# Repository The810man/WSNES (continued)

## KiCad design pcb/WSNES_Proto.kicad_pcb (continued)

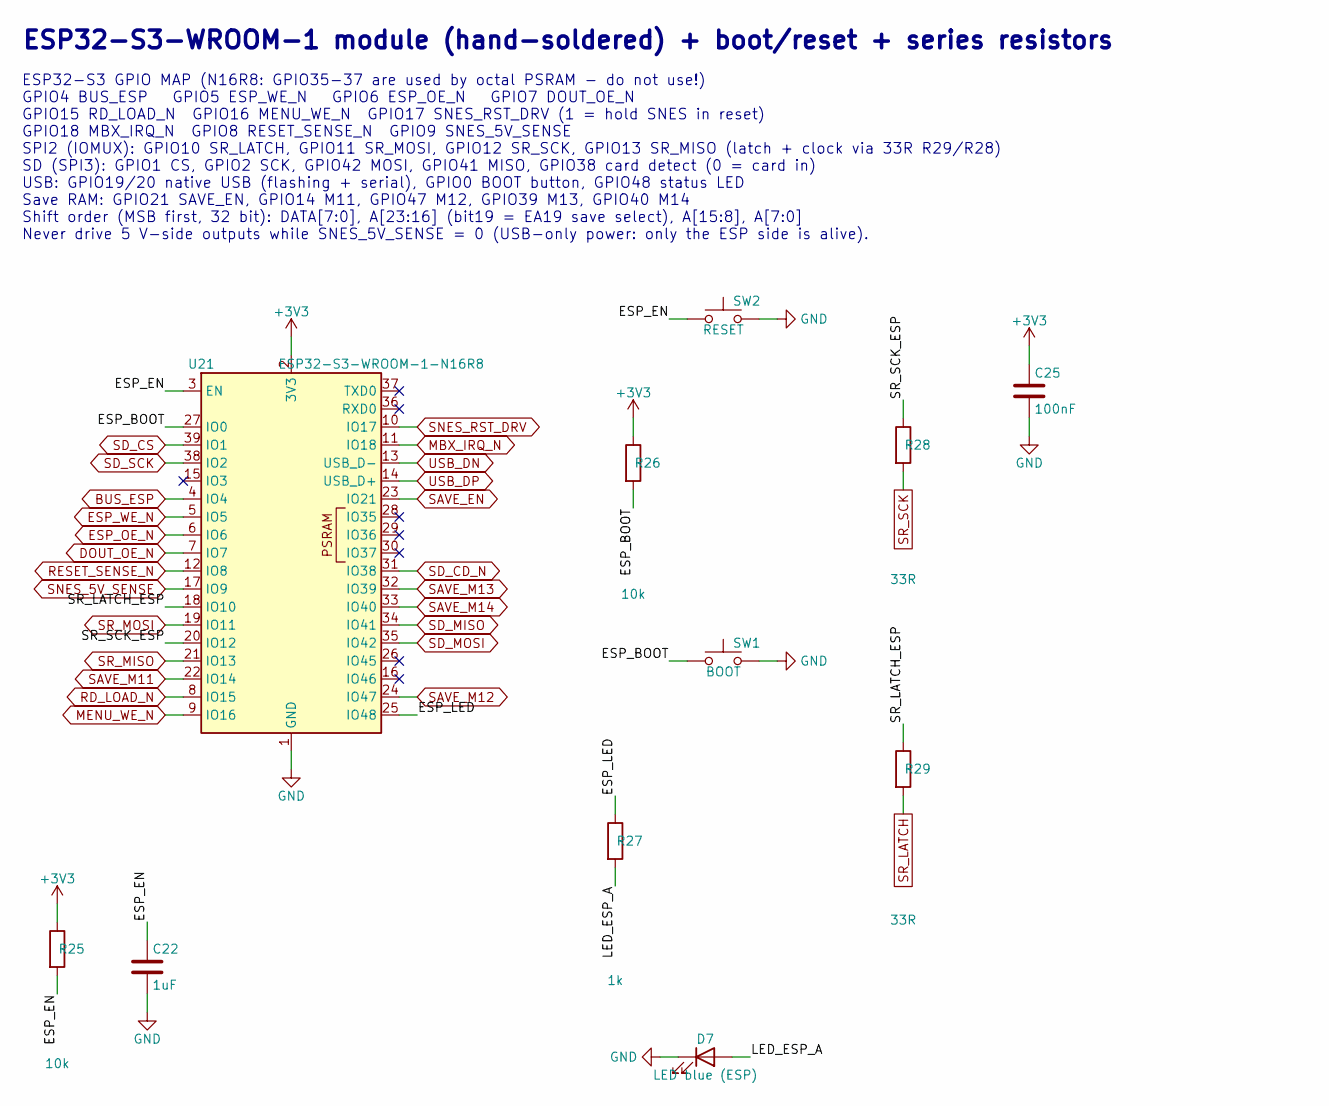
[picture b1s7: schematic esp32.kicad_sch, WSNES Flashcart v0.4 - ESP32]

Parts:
C22: 1uF; C_0603_1608Metric; MPN CL10A105KB8NNNC; LCSC C15849
C25: 100nF; C_0603_1608Metric; MPN CC0603KRX7R9BB104; LCSC C14663
D7: LED blue (ESP); LED_0603_1608Metric; MPN KT-0603B; LCSC C2288
R25, R26: 10k; R_0603_1608Metric; MPN 0603WAF1002T5E; LCSC C25804
R27: 1k; R_0603_1608Metric; MPN 0603WAF1001T5E; LCSC C21190
R28, R29: 33R; R_0603_1608Metric; MPN 0603WAF330JT5E; LCSC C23140
SW1: BOOT; SW_SPST_PTS810; MPN PTS810SJK250SMTRLFS; LCSC C221896
SW2: RESET; SW_SPST_PTS810; MPN PTS810SJK250SMTRLFS; LCSC C221896
U21: ESP32-S3-WROOM-1-N16R8; ESP32-S3-WROOM-1; MPN ESP32-S3-WROOM-1-N16R8; LCSC C2913202

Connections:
+3V3: C25.1, R25.1, R26.1, U21.2 (3V3); also elsewhere on the board
/ESP32/ESP_BOOT: R26.2, SW1.1, U21.27 (IO0)
/ESP32/ESP_EN: C22.1, R25.2, SW2.1, U21.3 (EN)
/ESP32/ESP_LED: R27.1, U21.25 (IO48)
/ESP32/LED_ESP_A: D7.2 (A), R27.2
/ESP32/SR_LATCH_ESP: R29.1, U21.18 (IO10)
/ESP32/SR_SCK_ESP: R28.1, U21.20 (IO12)
BUS_ESP: U21.4 (IO4); also elsewhere on the board
DOUT_OE_N: U21.7 (IO7); also elsewhere on the board
ESP_OE_N: U21.6 (IO6); also elsewhere on the board
ESP_WE_N: U21.5 (IO5); also elsewhere on the board
GND: C22.2, C25.2, D7.1 (K), SW1.2, SW2.2, U21.1 (GND), U21.40 (GND), U21.41 (GND); also elsewhere on the board
MBX_IRQ_N: U21.11 (IO18); also elsewhere on the board
MENU_WE_N: U21.9 (IO16); also elsewhere on the board
RD_LOAD_N: U21.8 (IO15); also elsewhere on the board
RESET_SENSE_N: U21.12 (IO8); also elsewhere on the board
SAVE_EN: U21.23 (IO21); also elsewhere on the board
SAVE_M11: U21.22 (IO14); also elsewhere on the board
SAVE_M12: U21.24 (IO47); also elsewhere on the board
SAVE_M13: U21.32 (IO39); also elsewhere on the board
SAVE_M14: U21.33 (IO40); also elsewhere on the board
SD_CD_N: U21.31 (IO38); also elsewhere on the board
SD_CS: U21.39 (IO1); also elsewhere on the board
SD_MISO: U21.34 (IO41); also elsewhere on the board
SD_MOSI: U21.35 (IO42); also elsewhere on the board
SD_SCK: U21.38 (IO2); also elsewhere on the board
SNES_5V_SENSE: U21.17 (IO9); also elsewhere on the board
SNES_RST_DRV: U21.10 (IO17); also elsewhere on the board
SR_LATCH: R29.2; also elsewhere on the board
SR_MISO: U21.21 (IO13); also elsewhere on the board
SR_MOSI: U21.19 (IO11); also elsewhere on the board
SR_SCK: R28.2; also elsewhere on the board
USB_DN: U21.13 (USB_D-); also elsewhere on the board
USB_DP: U21.14 (USB_D+); also elsewhere on the board

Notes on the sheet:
ESP32-S3-WROOM-1 module (hand-soldered) + boot/reset + series resistors
ESP32-S3 GPIO MAP (N16R8: GPIO35-37 are used by octal PSRAM - do not use!) GPIO4 BUS_ESP GPIO5 ESP_WE_N GPIO6 ESP_OE_N GPIO7 DOUT_OE_N GPIO15 RD_LOAD_N GPIO16 MENU_WE_N GPIO17 SNES_RST_DRV (1 = hold SNES in reset) GPIO18 MBX_IRQ_N GPIO8 RESET_SENSE_N GPIO9 SNES_5V_SENSE SPI2 (IOMUX): GPIO10 SR_LATC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

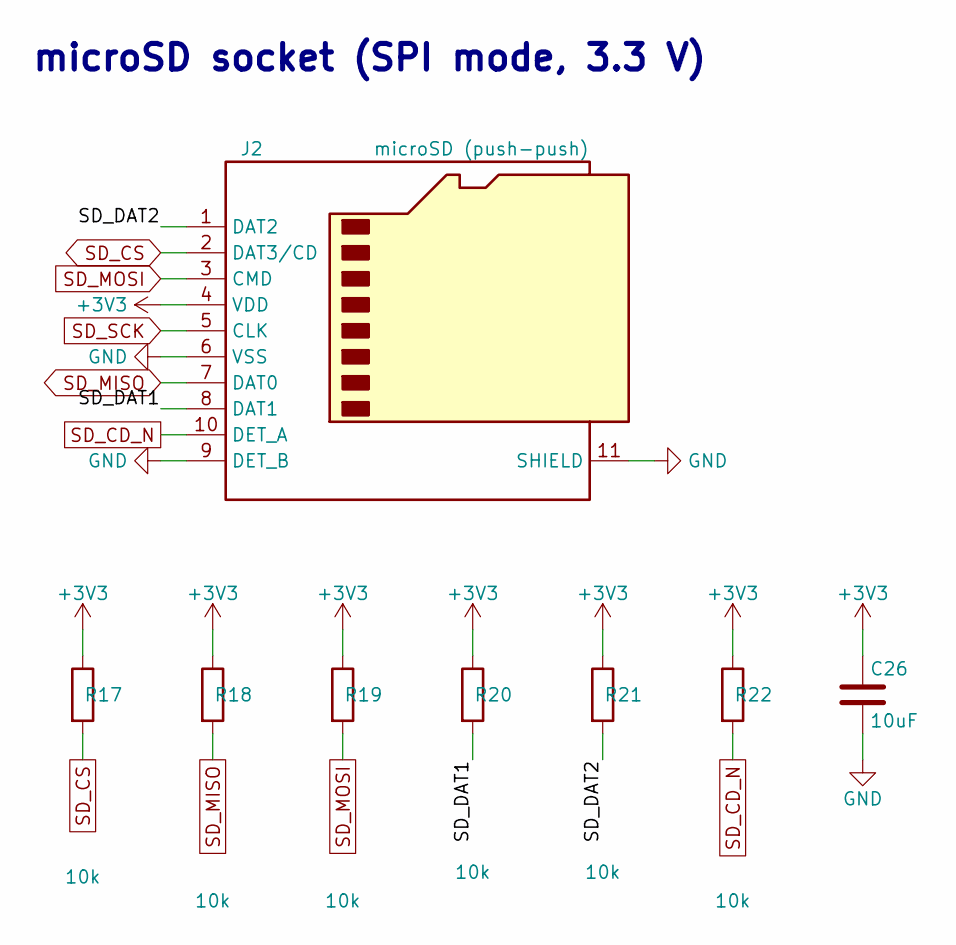
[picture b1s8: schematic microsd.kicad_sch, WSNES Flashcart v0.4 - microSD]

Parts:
C26: 10uF; C_0805_2012Metric; MPN CL21A106KAYNNNE; LCSC C15850
J2: microSD (push-push); microSD_HC_Hirose_DM3AT-SF-PEJM5; MPN DM3AT-SF-PEJM5; LCSC C114218
R17, R18, R19, R20, R21, R22: 10k; R_0603_1608Metric; MPN 0603WAF1002T5E; LCSC C25804

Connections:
+3V3: C26.1, J2.4 (VDD), R17.1, R18.1, R19.1, R20.1, R21.1, R22.1; also elsewhere on the board
/microSD/SD_DAT1: J2.8 (DAT1), R20.2
/microSD/SD_DAT2: J2.1 (DAT2), R21.2
GND: C26.2, J2.6 (VSS), J2.9 (DET_B), J2.11 (SHIELD); also elsewhere on the board
SD_CD_N: J2.10 (DET_A), R22.2; also elsewhere on the board
SD_CS: J2.2 (DAT3/CD), R17.2; also elsewhere on the board
SD_MISO: J2.7 (DAT0), R18.2; also elsewhere on the board
SD_MOSI: J2.3 (CMD), R19.2; also elsewhere on the board
SD_SCK: J2.5 (CLK); also elsewhere on the board

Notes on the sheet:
microSD socket (SPI mode, 3.3 V)

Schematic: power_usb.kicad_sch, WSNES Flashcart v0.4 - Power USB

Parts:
C1, C2: 22uF; C_1206_3216Metric; MPN CL31A226KAHNNNE; LCSC C12891
C23: 10uF; C_0805_2012Metric; MPN CL21A106KAYNNNE; LCSC C15850
C24: 22uF; C_0805_2012Metric; MPN CL21A226MAQNNNE; LCSC C45783
D1, D6: 1N5819WS; D_SOD-323; MPN 1N5819WS; LCSC C191023
D2: LED red (5V); LED_0603_1608Metric; MPN KT-0603R; LCSC C2286
J5: USB-C; USB_C_Receptacle_HRO_TYPE-C-31-M-12; MPN TYPE-C-31-M-12; LCSC C165948
R5: 1k; R_0603_1608Metric; MPN 0603WAF1001T5E; LCSC C21190
R23, R24: 5.1k; R_0603_1608Metric; MPN 0603WAF5101T5E; LCSC C23186
U22: AP2112K-3.3; SOT-23-5; MPN AP2112K-3.3TRG1; LCSC C51118
U23: USBLC6-2SC6; SOT-23-6; MPN USBLC6-2SC6; LCSC C7519

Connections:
+3V3: C24.1, U22.5 (VOUT); also elsewhere on the board
+5V: C2.1, D1.2 (A), R5.1; also elsewhere on the board
/Power_USB/ESP_5V: C1.1, C23.1, D1.1 (K), D6.1 (K), U22.1 (VIN), U22.3 (EN)
/Power_USB/LED_PWR_A: D2.2 (A), R5.2
/Power_USB/USB_CC1: J5.A5 (CC1), R23.1
/Power_USB/USB_CC2: J5.B5 (CC2), R24.1
/Power_USB/VBUS: D6.2 (A), J5.A4 (VBUS), J5.A9 (VBUS), J5.B4 (VBUS), J5.B9 (VBUS), U23.5 (VBUS)
GND: C1.2, C2.2, C23.2, C24.2, D2.1 (K), J5.A1 (GND), J5.A12 (GND), J5.B1 (GND), J5.B12 (GND), J5.S1 (SHIELD), R23.2, R24.2, U22.2 (GND), U23.2 (GND); also elsewhere on the board
USB_DN: J5.A7 (D-), J5.B7 (D-), U23.3 (I/O2), U23.4 (I/O2); also elsewhere on the board
USB_DP: J5.A6 (D+), J5.B6 (D+), U23.1 (I/O1), U23.6 (I/O1); also elsewhere on the board

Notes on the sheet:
Power: SNES 5 V, USB-C (ESD, CC), 3.3 V LDO
SNES +5V and USB VBUS meet at ESP_5V through D1 / D6 (Schottky OR). U22 makes +3V3 for the ESP, the SD card and U14. U23 USBLC6 protects D+, D- and VBUS at the connector.

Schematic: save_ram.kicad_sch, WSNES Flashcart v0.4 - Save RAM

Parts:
BT1: CR2032; BatteryHolder_MYOUNG_BS-07-A1BJ001_CR2032; MPN BS-07-A1BJ001; LCSC C2979167
C18, C19, C20, C21: 100nF; C_0603_1608Metric; MPN CC0603KRX7R9BB104; LCSC C14663
D4: BAT54C; SOT-23; MPN BAT54C; LCSC C466637
R6, R9: 1k; R_0603_1608Metric; MPN 0603WAF1001T5E; LCSC C21190
R7: 100k; R_0603_1608Metric; MPN 0603WAF1003T5E; LCSC C25803
U16: CY62128ELL-45SXI (save, 32K used); SOP-32_11.305x20.495mm_P1.27mm; MPN CY62128ELL-45SXI; LCSC C2953613
U17: 74HCT138; TSSOP-16_4.4x5mm_P0.65mm; MPN SN74HCT138PWR; LCSC C8115
U18, U19: 74HCT08; TSSOP-14_4.4x5mm_P0.65mm; MPN SN74HCT08PWR; LCSC C8181
U20: MCP100-450; SOT-23; MPN MCP100T-450I/TT; LCSC C134467

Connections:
+5V: C19.1, C20.1, C21.1, D4.1, U17.16 (VCC), U18.14 (VCC), U19.14 (VCC), U20.2 (VDD); also elsewhere on the board
/Save_RAM/PWR_OK: R6.1, U20.1 (~RST)
/Save_RAM/SAVE_CE2: R6.2, R7.1, U16.30 (CS2/CE2)
/Save_RAM/SAVE_G1: U17.6 (E2), U18.8
/Save_RAM/SV_A11: U16.25 (A11), U19.3
/Save_RAM/SV_A12: U16.4 (A12), U19.6
/Save_RAM/SV_A13: U16.28 (A13), U19.8
/Save_RAM/SV_A14: U16.3 (A14), U19.11
/Save_RAM/VBAT: BT1.1 (+), R9.1
/Save_RAM/VBAT_R: D4.2, R9.2
/Save_RAM/VSAVE: C18.1, D4.3, U16.32 (VCC)
BUS_ESP_N: U18.10; also elsewhere on the board
DBUF_OE_N: U18.6; also elsewhere on the board
DB_ROM_N: U18.4; also elsewhere on the board
GND: BT1.2 (-), C18.2, C19.2, C20.2, C21.2, R7.2, U16.2 (A16), U16.16 (GND), U16.31 (A15), U17.8 (GND), U18.7 (GND), U18.12, U18.13, U19.7 (GND), U20.3 (VSS); also elsewhere on the board
ROM_WE_OK_N: U18.2; also elsewhere on the board
SA0: U16.12 (A0); also elsewhere on the board
SA1: U16.11 (A1); also elsewhere on the board
SA2: U16.10 (A2); also elsewhere on the board
SA3: U16.9 (A3); also elsewhere on the board
SA4: U16.8 (A4); also elsewhere on the board
SA5: U16.7 (A5); also elsewhere on the board
SA6: U16.6 (A6); also elsewhere on the board
SA7: U16.5 (A7); also elsewhere on the board
SA8: U16.27 (A8); also elsewhere on the board
SA9: U16.26 (A9); also elsewhere on the board
SA10: U16.23 (A10); also elsewhere on the board
SA11: U19.1; also elsewhere on the board
SA12: U19.4; also elsewhere on the board
SA13: U19.9; also elsewhere on the board
SA14: U19.12; also elsewhere on the board
SAVE_CE_N: U16.22 (~CS1/~CE1); also elsewhere on the board
SAVE_EN: U18.9; also elsewhere on the board
SAVE_M11: U19.2; also elsewhere on the board
SAVE_M12: U19.5; also elsewhere on the board
SAVE_M13: U19.10; also elsewhere on the board
SAVE_M14: U19.13; also elsewhere on the board
SAVE_SEL_N: U17.7 (~Y7), U18.1, U18.5; also elsewhere on the board
SD0: U16.13 (DQ0); also elsewhere on the board
SD1: U16.14 (DQ1); also elsewhere on the board
SD2: U16.15 (DQ2); also elsewhere on the board
SD3: U16.17 (DQ3); also elsewhere on the board
SD4: U16.18 (DQ4); also elsewhere on the board
SD5: U16.19 (DQ5); also elsewhere on the board
SD6: U16.20 (DQ6); also elsewhere on the board
SD7: U16.21 (DQ7); also elsewhere on the board
SNES_A15: U17.5 (~E1); also elsewhere on the board
SNES_A20: U17.1 (A0); also elsewhere on the board
SNES_A21: U17.2 (A1); also elsewhere on the board
SNES_A22: U17.3 (A2); also elsewhere on the board
SNES_ROMSEL_N: U17.4 (~E0); also elsewhere on the board
SRAM_OE_N: U16.24 (~OE); also elsewhere on the board
SRAM_WE_N: U16.29 (~WE); also elsewhere on the board
WE_GATE_N: U18.3; also elsewhere on the board

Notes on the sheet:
Battery-backed save RAM (LoROM $70-$7D:0000-7FFF)
Save RAM: CY62128E at LoROM $70-$7D/$F0-$FF:0000-7FFF, CR2032 backed, write-protected below 4.4 V
U17 decodes the LoROM save area: A22=A21=A20=1, A15=0, /ROMSEL=0 -> SAVE_SEL_N (only in SNES mode and when SAVE_EN=1). U19 masks A11-A14 with SAVE_M11..M14 (ESP GPIOs) so the RAM mirrors at the header size (2 KB: all 0, 8 KB: M11+M12, 32 KB: all 1). Some games check the mirroring (anti-copier), so 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

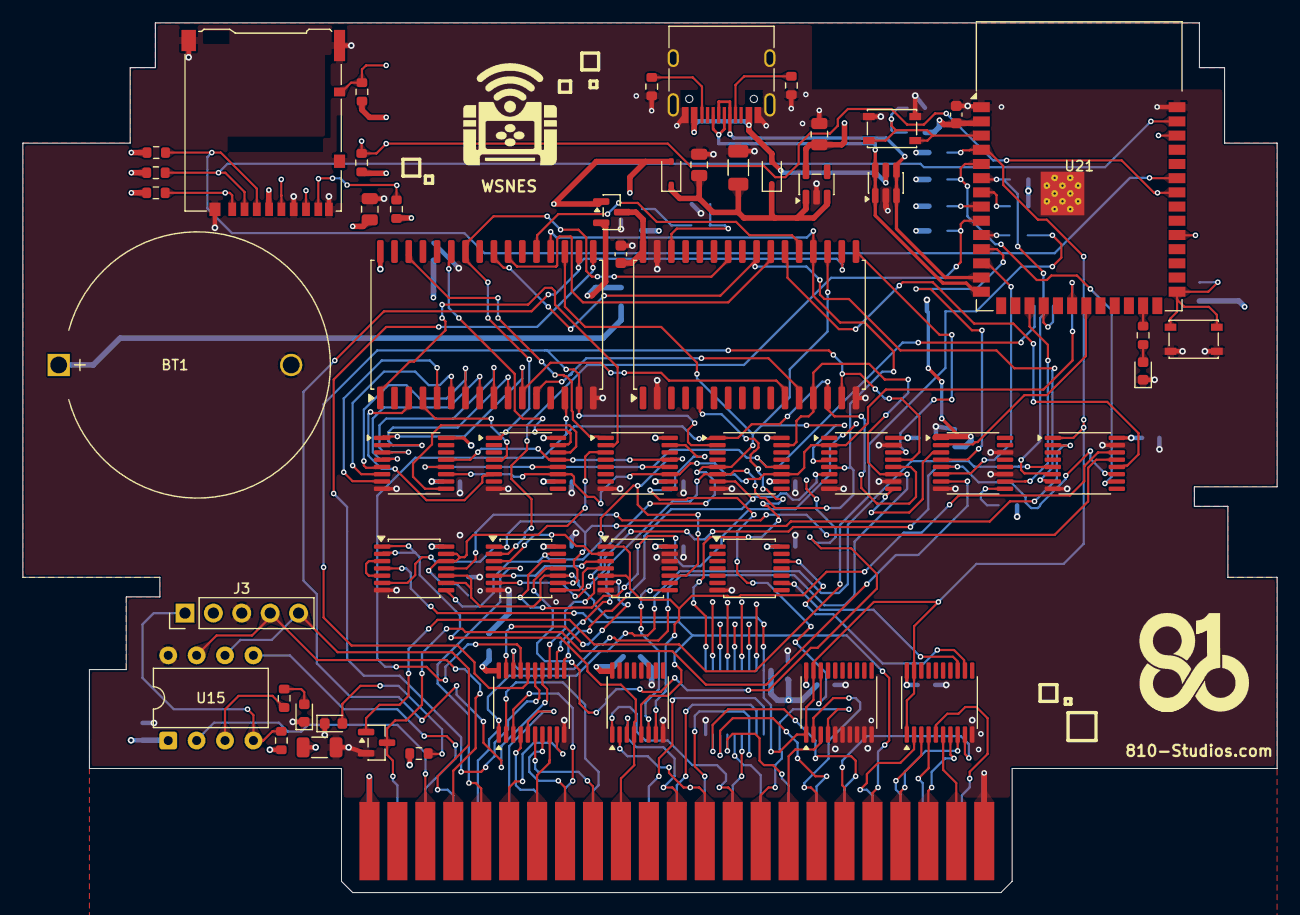
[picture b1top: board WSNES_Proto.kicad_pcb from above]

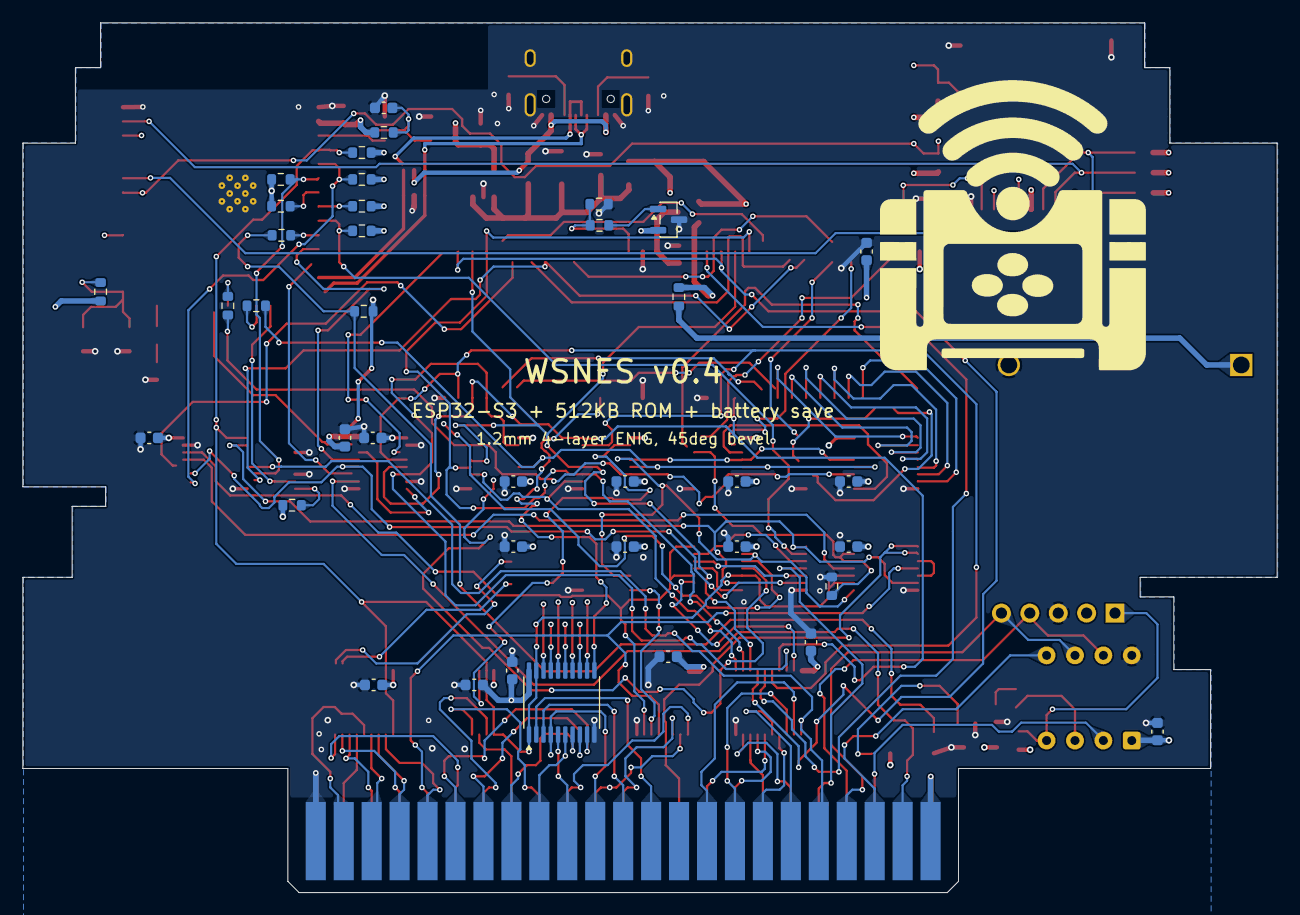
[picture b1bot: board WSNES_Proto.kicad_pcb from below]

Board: 4 copper layers, 112.2 x 77.8 mm, 92 parts (38 on the bottom side), 143 nets.

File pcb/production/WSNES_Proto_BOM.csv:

"Refs","Value","Footprint","Manufacturer","MPN","LCSC","Assembly","Qty","Notes"
"BT1","CR2032","Battery:BatteryHolder_MYOUNG_BS-07-A1BJ001_CR2032","MYOUNG","BS-07-A1BJ001","C2979167","HAND","1","holder only; add one CR2032 cell"
"C1,C2","22uF","Capacitor_SMD:C_1206_3216Metric","Samsung","CL31A226KAHNNNE","C12891","JLC","2",""
"C3-C21,C25","100nF","Capacitor_SMD:C_0603_1608Metric","YAGEO","CC0603KRX7R9BB104","C14663","JLC","20",""
"C22","1uF","Capacitor_SMD:C_0603_1608Metric","Samsung","CL10A105KB8NNNC","C15849","JLC","1",""
"C23,C26","10uF","Capacitor_SMD:C_0805_2012Metric","Samsung","CL21A106KAYNNNE","C15850","JLC","2",""
"C24","22uF","Capacitor_SMD:C_0805_2012Metric","Samsung","CL21A226MAQNNNE","C45783","JLC","1",""
"D1,D6","1N5819WS","Diode_SMD:D_SOD-323","Hottech","1N5819WS","C191023","JLC","2",""
"D2","LED red (5V)","LED_SMD:LED_0603_1608Metric","KENTO","KT-0603R","C2286","JLC","1",""
"D3","LED green (CIC OK)","LED_SMD:LED_0603_1608Metric","KENTO","KT-0603G","C12624","JLC","1",""
"D4","BAT54C","Package_TO_SOT_SMD:SOT-23","High Diode","BAT54C","C466637","JLC","1",""
"D7","LED blue (ESP)","LED_SMD:LED_0603_1608Metric","KENTO","KT-0603B","C2288","JLC","1",""
"J2","microSD (push-push)","Connector_Card:microSD_HC_Hirose_DM3AT-SF-PEJM5","Hirose","DM3AT-SF-PEJM5","C114218","JLC","1",""
"J3","ICSP (PIC, optional)","Connector_PinHeader_2.54mm:PinHeader_1x05_P2.54mm_Vertical","DEALON","DM254R-11-05-85","C2935976","HAND","1","optional, only for flashing the PIC in circuit"
"J5","USB-C","Connector_USB:USB_C_Receptacle_HRO_TYPE-C-31-M-12","HRO","TYPE-C-31-M-12","C165948","JLC","1",""
"P1","SNES_Cart_Edge","WSNES_Proto:SNES_Cart_Edge_46P_P2.50mm","","","","PCB","1",""
"Q1","2N7002","Package_TO_SOT_SMD:SOT-23","JSCJ","2N7002","C8545","JLC","1",""
"R1","100R","Resistor_SMD:R_0603_1608Metric","UNI-ROYAL","0603WAF1000T5E","C22775","JLC","1",""
"R2,R3,R8,R10-R22,R25,R26","10k","Resistor_SMD:R_0603_1608Metric","UNI-ROYAL","0603WAF1002T5E","C25804","JLC","18",""
"R4-R6,R9,R27","1k","Resistor_SMD:R_0603_1608Metric","UNI-ROYAL","0603WAF1001T5E","C21190","JLC","5",""
"R7","100k","Resistor_SMD:R_0603_1608Metric","UNI-ROYAL","0603WAF1003T5E","C25803","JLC","1",""
"R23,R24","5.1k","Resistor_SMD:R_0603_1608Metric","UNI-ROYAL","0603WAF5101T5E","C23186","JLC","2",""
"R28,R29","33R","Resistor_SMD:R_0603_1608Metric","UNI-ROYAL","0603WAF330JT5E","C23140","JLC","2",""
"SW1","BOOT","Button_Switch_SMD:SW_SPST_PTS810","C&K","PTS810SJK250SMTRLFS","C221896","JLC","1","replaces the out-of-stock PTS810SJM (1.6 N); same footprint, 2.6 N"
"SW2","RESET","Button_Switch_SMD:SW_SPST_PTS810","C&K","PTS810SJK250SMTRLFS","C221896","JLC","1","replaces the out-of-stock PTS810SJM (1.6 N); same footprint, 2.6 N"
"U1","CY62148ELL-55SXI (ROM, 512K x 8)","Package_SO:SOP-32_11.305x20.495mm_P1.27mm","Infineon (Cypress)","CY62148ELL-55SXI","C2953576","JLC","1","replaces the out-of-stock AS6C4008-55SIN (C1350086). Same 450-mil SOIC-32 land pattern, JEDEC pinout, 4.5-5.5 V, 55 ns. Only 5 in stock at LCSC on 2026-11-18: order early, or buy and hand-solder it"
"U2-U4","74AHCT541","Package_SO:TSSOP-20_4.4x6.5mm_P0.65mm","Nexperia","74AHCT541PW,118","C84548","JLC","3",""
"U5","74AHCT245","Package_SO:TSSOP-20_4.4x6.5mm_P0.65mm","Texas Instruments","SN74AHCT245PWR","C10910","JLC","1","replaces the out-of-stock 74AHCT245PW,118 (C173388); same TSSOP-20 pinout"
"U6","74HCT00","Package_SO:TSSOP-14_4.4x5mm_P0.65mm","Nexperia","74HCT00PW,118","C8206","JLC","1",""
"U7","74HCT32","Package_SO:TSSOP-14_4.4x5mm_P0.65mm","Texas Instruments","SN74HCT32PWR","C132266","JLC","1",""
"U8","74AHCT157","Package_SO:TSSOP-16_4.4x5mm_P0.65mm","Texas Instruments","SN74AHCT157PWR","C2674471","JLC","1","AHCT instead of HCT: faster /ROMSEL -> SRAM /CE path (FastROM)"
"U9-U12","74HCT595","Package_SO:TSSOP-16_4.4x5mm_P0.65mm","MDD","74HCT595PW","C54411086","JLC","4",""
"U13","74HCT165","Package_SO:TSSOP-16_4.4x5mm_P0.65mm","Texas Instruments","SN74HCT165PWR","C3304572","JLC","1","replaces the out-of-stock 74HCT165PW,118 (C547409); same TSSOP-16 pinout. Must stay HCT (CP and /PL are 3.3 V signals)"
"U14","CD74HC4050","Package_SO:TSSOP-16_4.4x5mm_P0.65mm","Texas Instruments","CD74HC4050PWR","C352825","JLC","1",""
"U15","PIC12F629 (SuperCIC key)","Package_DIP:DIP-8_W7.62mm","Microchip","PIC12F629-I/P","C9785","HAND","1",""
"U16","CY62128ELL-45SXI (save, 32K used)","Package_SO:SOP-32_11.305x20.495mm_P1.27mm","Infineon (Cypress)","CY62128ELL-45SXI","C2953613","JLC","1","replaces the out-of-stock AS6C1008-55SIN (C1351203); same pinout and 450-mil SOP-32. Rated 4.5-5.5 V but VSAVE is ~0.35 V below +5V (BAT54C), so it is only in spec with >= 4.9 V from the console. Data retention from 2.0 V (CR2032 is fine). Prefer the AS6C1008 (2.7-5.5 V) when stocked"
"U17","74HCT138","Package_SO:TSSOP-16_4.4x5mm_P0.65mm","Texas Instruments","SN74HCT138PWR","C8115","JLC","1",""
"U18,U19","74HCT08","Package_SO:TSSOP-14_4.4x5mm_P0.65mm","Texas Instruments","SN74HCT08PWR","C8181","JLC","2",""
"U20","MCP100-450","Package_TO_SOT_SMD:SOT-23","Microchip","MCP100T-450I/TT","C134467","JLC","1",""
"U21","ESP32-S3-WROOM-1-N16R8","RF_Module:ESP32-S3-WROOM-1","Espressif","ESP32-S3-WROOM-1-N16R8","C2913202","HAND","1",""
"U22","AP2112K-3.3","Package_TO_SOT_SMD:SOT-23-5","Diodes Inc.","AP2112K-3.3TRG1","C51118","JLC","1",""
"U23","USBLC6-2SC6","Package_TO_SOT_SMD:SOT-23-6","STMicroelectronics","USBLC6-2SC6","C7519","JLC","1",""

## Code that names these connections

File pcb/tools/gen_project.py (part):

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        ('SIGNAL FLOW\n'
         'SNES edge (Edge_CIC) -> SNES_A* / SNES_D* / SNES_RD_N / SNES_WR_N -> SNES_Buffers (U2-U5) -> SA* / SD* -> ROM SRAM U1 and Save RAM U16\n'
         'ESP32 -> SPI (SR_SCK / SR_MOSI / SR_LATCH via 33R) -> ESP_Serial (U9-U12 595 drive SA* / SD*, U13 165 reads SD* back -> SR_MISO)\n'
         'BUS_ESP (one GPIO, pulled high) selects the owner: 0 = SNES plays (U2-U5 on), 1 = ESP loads (U9-U12 on). ROM_Glue muxes /CE /OE /WE.\n'
         'Level_Reset shifts 5 V status lines down to 3.3 V for the ESP and holds the SNES in reset until the firmware releases it.\n'
         'Net names: labels that cross sheets are GLOBAL labels (same net name everywhere); sheet-internal nets are local (/Sheet/NET).\n'
         'Every IC has its 100 nF decoupling cap on its own sheet.', 1.5, False),
    ],
    'rom': [
        ('BUS OWNERSHIP (single GPIO BUS_ESP, pulled HIGH = ESP owns bus at power-up)\n'
         'BUS_ESP=0 (SNES plays): U2-U4 drive SA*, U5 passes data when ROM_SEL_N=0,\n'
         '   SRAM /CE=ROM_SEL_N, /OE=SNES /RD, /WE=SNES_WE_N (only if MENU_WE_N=0).\n'
         'BUS_ESP=1 (ESP loads): U9-U11 drive SA*, U12 drives SD* when DOUT_OE_N=0,\n'
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    ],
    'esp': [
        ('ESP32-S3 GPIO MAP (N16R8: GPIO35-37 are used by octal PSRAM - do not use!)\n'
         'GPIO4 BUS_ESP   GPIO5 ESP_WE_N   GPIO6 ESP_OE_N   GPIO7 DOUT_OE_N\n'
         'GPIO15 RD_LOAD_N  GPIO16 MENU_WE_N  GPIO17 SNES_RST_DRV (1 = hold SNES in reset)\n'
         'GPIO18 MBX_IRQ_N  GPIO8 RESET_SENSE_N  GPIO9 SNES_5V_SENSE\n'
         'SPI2 (IOMUX): GPIO10 SR_LATCH, GPIO11 SR_MOSI, GPIO12 SR_SCK, GPIO13 SR_MISO (latch + clock via 33R R29/R28)\n'
         'SD (SPI3): GPIO1 CS, GPIO2 SCK, GPIO42 MOSI, GPIO41 MISO, GPIO38 card detect (0 = card in)\n'
         'USB: GPIO19/20 native USB (flashing + serial), GPIO0 BOOT button, GPIO48 status LED\n'
         'Save RAM: GPIO21 SAVE_EN, GPIO14 M11, GPIO47 M12, GPIO39 M13, GPIO40 M14\n'
         'Shift order (MSB first, 32 bit): DATA[7:0], A[23:16] (bit19 = EA19 save select), A[15:8], A[7:0]\n'
         'Never drive 5 V-side outputs while SNES_5V_SENSE = 0 (USB-only power: only the ESP side is alive).', 1.5, False),
    ],
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    'save': [
        ('Save RAM: CY62128E at LoROM $70-$7D/$F0-$FF:0000-7FFF, CR2032 backed, write-protected below 4.4 V', 2.0, True),
        ('U17 decodes the LoROM save area: A22=A21=A20=1, A15=0, /ROMSEL=0 -> SAVE_SEL_N (only in SNES mode and when SAVE_EN=1).\n'
         'U19 masks A11-A14 with SAVE_M11..M14 (ESP GPIOs) so the RAM mirrors at the header size (2 KB: all 0, 8 KB: M11+M12, 32 KB: all 1).\n'
         'Some games check the mirroring (anti-copier), so set the masks from the ROM header before releasing reset.\n'
         'ESP access: BUS_ESP=1, address bit EA19 (U11 QD) = 1 selects the save chip, 0 the ROM chip (set masks to 1 for full access).\n'
         'Power fail: U20 drives CE2 low below ~4.4 V, R7 holds it low when the cart is off -> no garbage writes, data kept by BT1.\n'
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
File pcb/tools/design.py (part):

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     datasheet='https://datasheet.lcsc.com/datasheet/pdf/51aeef03b794f8ed6a09b3f6c1179ead.pdf?productCode=C2953576')

# ---------------------------------------------------------------- glue logic (5 V, HCT inputs accept 3.3 V)
# U8 is AHCT (pin-compatible): it sits in the /ROMSEL -> SRAM /CE path and saves ~24 ns worst case
# against the HCT157 (34 -> 9.8 ns), which helps FastROM timing.
part('U8', '74xx', '74LS157', '74AHCT157', FP_TSSOP16, (256.54, 162.56),
     {1: 'BUS_ESP', 15: 'GND', 16: '+5V', 8: 'GND',
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     {1: 'ESP_BOOT', 2: 'GND'}, mpn='PTS810SJM250SMTRLFS')
part('R27', 'Device', 'R', '1k', FP_R, (599.44, 127.0), {1: 'ESP_LED', 2: 'LED_ESP_A'})
# v0.4: series termination for the two fast multi-drop lines from the ESP (SR_SCK drives 5 loads over ~96 mm,
# SR_LATCH 4 loads over ~81 mm). ~25 ohm GPIO + 33 ohm ~ the trace impedance, so no double clocking on ringing.
part('R28', 'Device', 'R', '33R', FP_R, (599.44, 154.94), {1: 'SR_SCK_ESP', 2: 'SR_SCK'}, note='series R at ESP')
part('R29', 'Device', 'R', '33R', FP_R, (599.44, 170.18), {1: 'SR_LATCH_ESP', 2: 'SR_LATCH'}, note='series R at ESP')
part('D7', 'Device', 'LED', 'LED blue (ESP)', FP_LED, (612.14, 139.7), {2: 'LED_ESP_A', 1: 'GND'})
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# 74HCT165PW,118 (C547409) are all at 0. Replaced by pin-compatible, in-stock parts (U1, U5, U13 below).
# U1 CY62148ELL-55SXI had only 5 pcs at LCSC on 2026-11-18: order it early, or hand-solder U1 if it runs out.
# U16 moved on 2026-11-17 from AS6C1008-55SIN (C1351203, 2.7-5.5 V, out of stock) to the in-stock CY62128ELL-45SXI:
# same JEDEC pinout and 450-mil SOIC-32, but 4.5-5.5 V. VSAVE sits one BAT54C drop below +5V, so it is only in
# spec while the console delivers about 4.9 V or more. Go back to the AS6C1008 when it is stocked again.
SOURCING = {
    'U1': ('Infineon (Cypress)', 'CY62148ELL-55SXI', 'C2953576'),   # was AS6C4008-55SIN (C1350086, out of stock)
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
